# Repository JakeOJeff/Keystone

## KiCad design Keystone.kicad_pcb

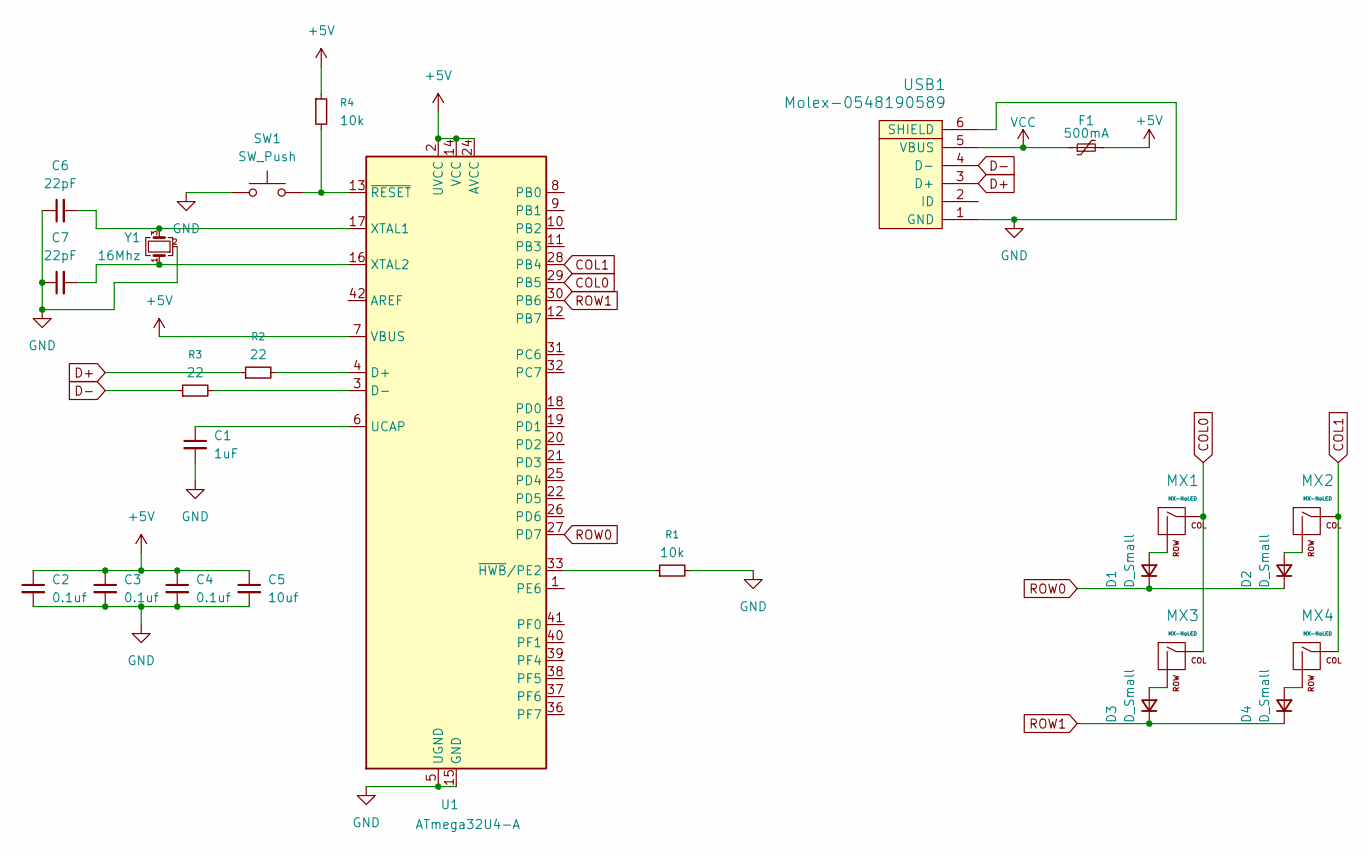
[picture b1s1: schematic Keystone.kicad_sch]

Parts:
C1: 1uF; C_0805_2012Metric
C2, C3, C4: 0.1uf; C_0805_2012Metric
C5: 10uf; C_0805_2012Metric
C6, C7: 22pF; C_0805_2012Metric
D1, D2, D3, D4: D_Small; D_SOD-123
F1: 500mA; Fuse_1206_3216Metric
MX1, MX2, MX3, MX4: MX-NoLED; MX-1U-NoLED
R1, R4: 10k; R_0805_2012Metric
R2, R3: 22; R_0805_2012Metric
SW1: SW_Push; SKQG-1155865
U1: ATmega32U4-A; TQFP-44_10x10mm_P0.8mm
USB1: Molex-0548190589
Y1: 16Mhz; Crystal_SMD_3225-4Pin_3.2x2.5mm

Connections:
+5V: C2.1, C3.1, C4.1, C5.1, F1.2, R4.1, U1.2 (UVCC), U1.7 (VBUS), U1.14 (VCC), U1.24 (AVCC), U1.34 (VCC), U1.44 (AVCC)
COL0: MX1.1 (COL), MX3.1 (COL), U1.29 (PB5)
COL1: MX2.1 (COL), MX4.1 (COL), U1.28 (PB4)
D+: R2.1, USB1.3 (D+)
D-: R3.1, USB1.4 (D-)
GND: C1.2, C2.2, C3.2, C4.2, C5.2, C6.1, C7.1, R1.2, SW1.1, U1.5 (UGND), U1.15 (GND), U1.23 (GND), U1.35 (GND), U1.43 (GND), USB1.1 (GND), USB1.6 (SHIELD), Y1.2 (G), Y1.4 (G)
unnamed: D1.2 (A), MX1.2 (ROW)
unnamed: D2.2 (A), MX2.2 (ROW)
unnamed: D3.2 (A), MX3.2 (ROW)
unnamed: D4.2 (A), MX4.2 (ROW)
unnamed: R2.2, U1.4 (D+)
unnamed: R3.2, U1.3 (D-)
unnamed: C1.1, U1.6 (UCAP)
unnamed: C6.2, U1.17 (XTAL1), Y1.3
unnamed: C7.2, U1.16 (XTAL2), Y1.1
unnamed: R1.1, U1.33 (~HWB/PE2)
unnamed: R4.2, SW1.2, U1.13 (~RESET)
ROW0: D1.1 (K), D2.1 (K), U1.27 (PD7)
ROW1: D3.1 (K), D4.1 (K), U1.30 (PB6)
VCC: F1.1, USB1.5 (VBUS)

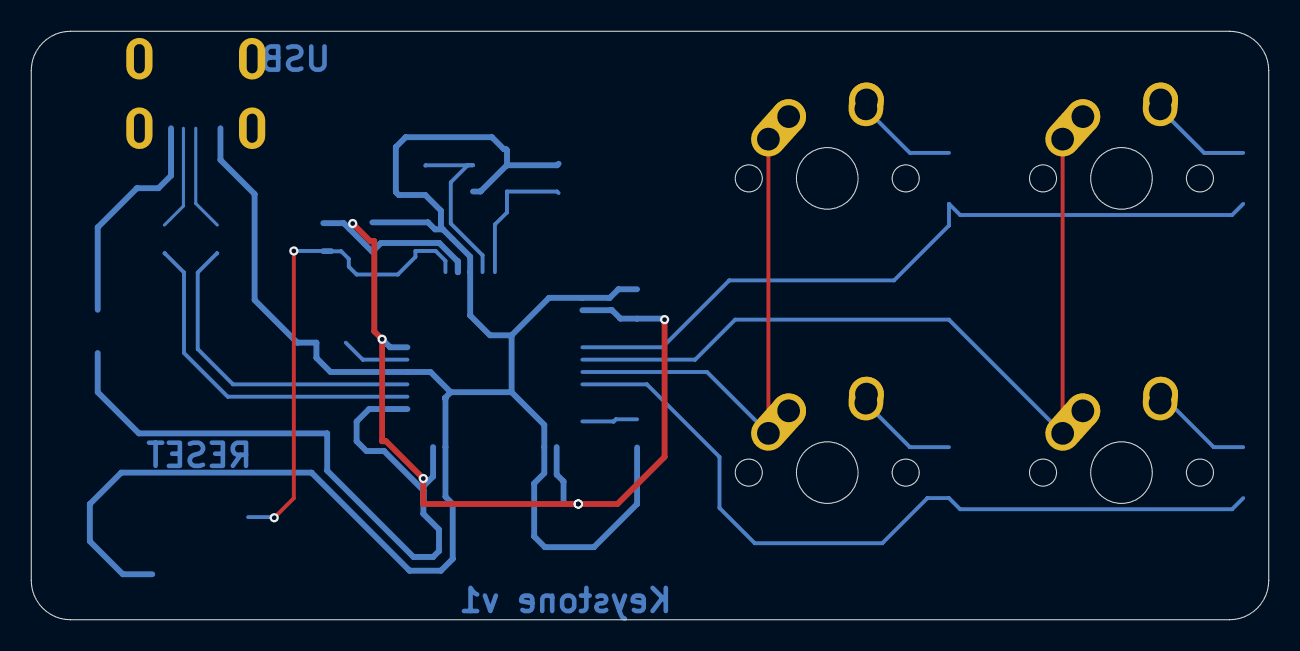
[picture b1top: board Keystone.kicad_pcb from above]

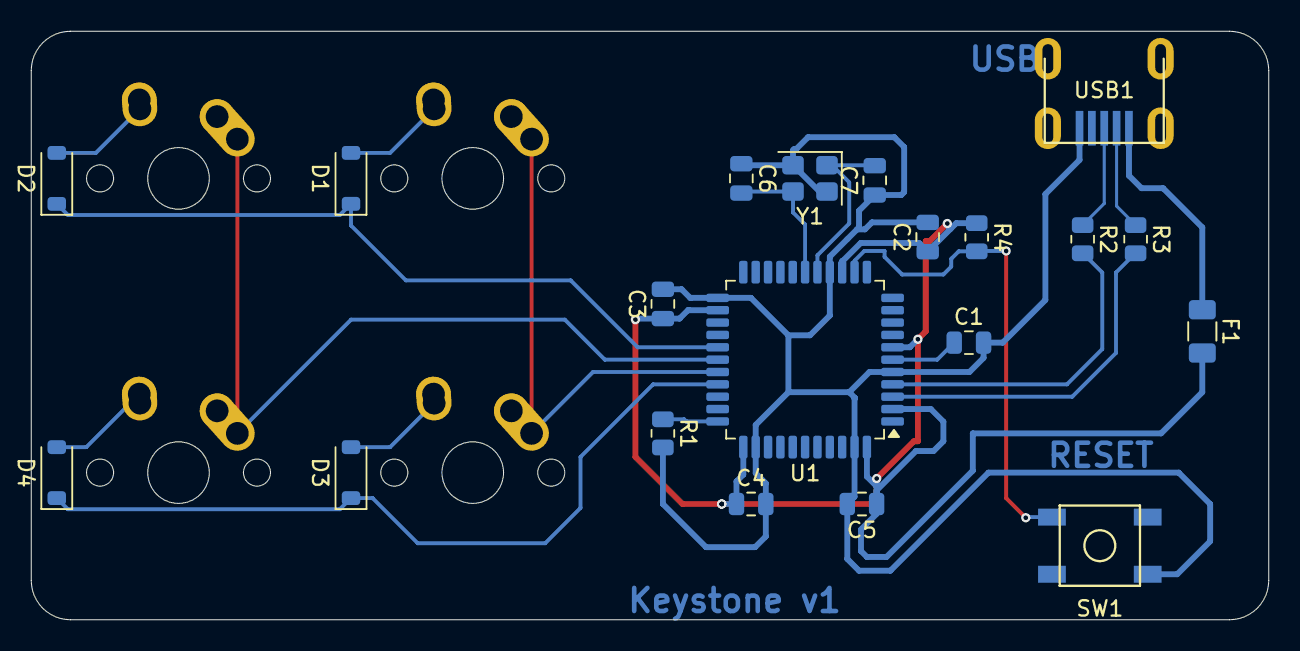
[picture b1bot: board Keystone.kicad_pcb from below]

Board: 2 copper layers, 80.1 x 38.1 mm, 24 parts (20 on the bottom side), 20 nets.

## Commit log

2026-06-09 init
2026-06-09 Added MX_Alps_Hybrid and Random-keyboard-parts libs
2026-06-09 Connected resistors to new schematic ATmega32U4-A
2026-06-10 Assigned footprints for the schematics
2026-06-12 Wired up components, realigned position
